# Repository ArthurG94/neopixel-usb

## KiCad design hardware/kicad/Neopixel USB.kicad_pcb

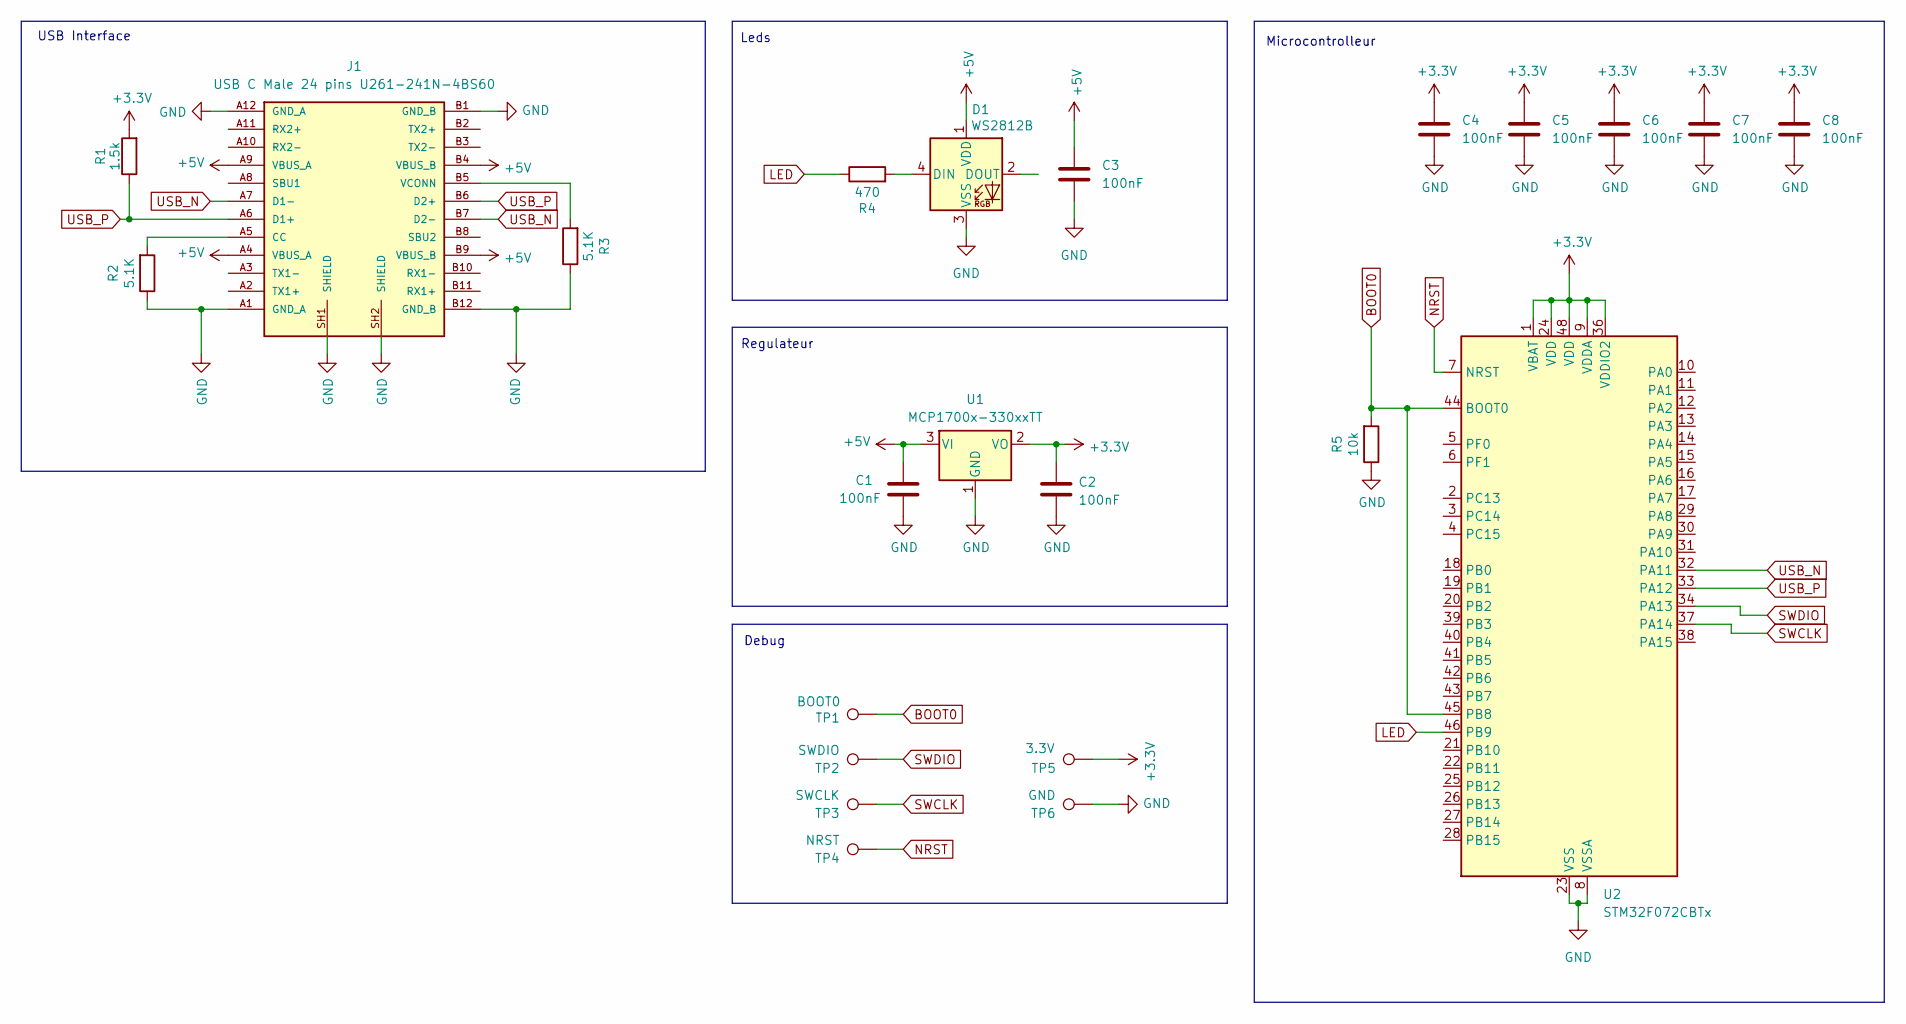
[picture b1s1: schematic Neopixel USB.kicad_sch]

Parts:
C1, C2, C3, C4, C5, C6, C7, C8: 100nF; C_0603_1608Metric; LCSC C14663
D1: WS2812B; LED_WS2812B_PLCC4_5.0x5.0mm_P3.2mm; LCSC C2843785
J1: USB C Male 24 pins U261-241N-4BS60; USB-C male 24 pins XKB_U261-241N-4BS60; LCSC C319150
R1: 1.5k; R_0603_1608Metric; LCSC C22843
R2, R3: 5.1K; R_0603_1608Metric; LCSC C23186
R4: 470; R_0603_1608Metric; LCSC C23179
R5: 10k; R_0603_1608Metric; LCSC C25804
TP1: BOOT0; TestPoint_Pad_D1.0mm_1
TP2: SWDIO; TestPoint_Pad_D1.0mm_1
TP3: SWCLK; TestPoint_Pad_D1.0mm_1
TP4: NRST; TestPoint_Pad_D1.0mm_1
TP5: 3.3V; TestPoint_Pad_D1.0mm_1
TP6: GND; TestPoint_Pad_D1.0mm_1
U1: MCP1700x-330xxTT; SOT-23
U2: STM32F072CBTx; LQFP-48_7x7mm_P0.5mm; LCSC C81720

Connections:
+3.3V: C2.1, C4.1, C5.1, C6.1, C7.1, C8.1, R1.2, TP5.1, U1.2 (VO), U2.1 (VBAT), U2.9 (VDDA), U2.24 (VDD), U2.36 (VDDIO2), U2.48 (VDD)
+5V: C1.1, C3.1, D1.1 (VDD), J1.A4 (VBUS_A), J1.A9 (VBUS_A), J1.B4 (VBUS_B), J1.B9 (VBUS_B), U1.3 (VI)
BOOT0: R5.2, TP1.1, U2.44 (BOOT0), U2.45 (PB8)
GND: C1.2, C2.2, C3.2, C4.2, C5.2, C6.2, C7.2, C8.2, D1.3 (VSS), J1.A1 (GND_A), J1.A12 (GND_A), J1.B1 (GND_B), J1.B12 (GND_B), J1.SH1 (SHIELD), J1.SH2 (SHIELD), R2.1, R3.1, R5.1, TP6.1, U1.1 (GND), U2.8 (VSSA), U2.23 (VSS), U2.35 (VSS), U2.47 (VSS)
LED: R4.1, U2.46 (PB9)
NRST: TP4.1, U2.7 (NRST)
unnamed: D1.4 (DIN), R4.2
unnamed: J1.A5 (CC), R2.2
unnamed: J1.B5 (VCONN), R3.2
SWCLK: TP3.1, U2.37 (PA14)
SWDIO: TP2.1, U2.34 (PA13)
USB_N: J1.A7 (D1-), J1.B7 (D2-), U2.32 (PA11)
USB_P: J1.A6 (D1+), J1.B6 (D2+), R1.1, U2.33 (PA12)

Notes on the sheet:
Debug
USB Interface
Leds
Microcontrolleur
Regulateur

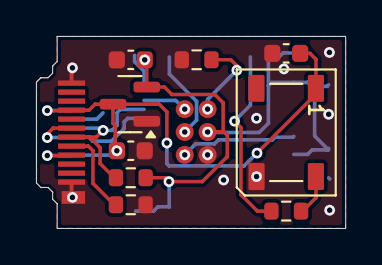
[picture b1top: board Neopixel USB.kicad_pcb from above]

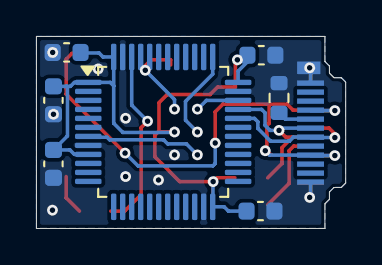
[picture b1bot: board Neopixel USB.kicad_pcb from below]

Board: 2 copper layers, 17.2 x 10.7 mm, 23 parts (7 on the bottom side), 13 nets.

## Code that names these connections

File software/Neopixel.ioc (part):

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Mcu.Name=STM32F072C(8-B)Tx
Mcu.Package=LQFP48
Mcu.UserName=STM32F072CBTx
PA11.Mode=Device
PA11.Signal=USB_DM
PA12.Mode=Device
PA12.Signal=USB_DP
PA13.Mode=Serial_Wire
PA13.Signal=SYS_SWDIO
PA14.Mode=Serial_Wire
PA14.Signal=SYS_SWCLK
PB9.Signal=S_TIM17_CH1
RCC.SYSCLKFreq_VALUE=48000000
RCC.SYSCLKSource=RCC_SYSCLKSOURCE_PLLCLK
board=custom

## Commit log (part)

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2025-07-08 First commit. kicad project and gerber added
2025-09-01 code working on linux
2026-04-27 Mise à jour du schema
2026-04-30 Restructuration du projet
2026-05-02 mise au propre du projet
